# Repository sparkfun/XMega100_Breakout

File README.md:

SparkFun XMega100 Breakout
========================================

[*SparkFun XMega100 Breakout (BOB-09546)*](https://www.sparkfun.com/products/9546)

This is a breakout board for the 100-pin TQFP package of Atmel’s ATxmega128A1. 
The ATxmega128A1 is a low power, high performance and peripheral rich CMOS 8/16-bit microcontroller based on the AVR enhanced RISC architecture.

Repository Contents
-------------------

* **/Firmware** - Example code 
* **/Hardware** - Eagle design files (.brd, .sch)
* **/Production** - Production panel files (.brd)

Documentation
--------------
* **[SparkFun Fritzing repo](https://github.com/sparkfun/Fritzing_Parts)** - Fritzing diagrams for SparkFun products.
* **[SparkFun 3D Model repo](https://github.com/sparkfun/3D_Models)** - 3D models of SparkFun products. 

License Information
-------------------
This product is _**open source**_! 

The **hardware** is released under [Creative Commons ShareAlike 4.0 International](https://creativecommons.org/licenses/by-sa/4.0/).

The **code** is beerware; if you see me (or any other SparkFun employee) at the local, and you've found our code helpful, please buy us a round!

Please use, reuse, and modify these files as you see fit. Please maintain attribution to SparkFun Electronics and release anything derivative under the same license.

Distributed as-is; no warranty is given.

- Your friends at SparkFun.

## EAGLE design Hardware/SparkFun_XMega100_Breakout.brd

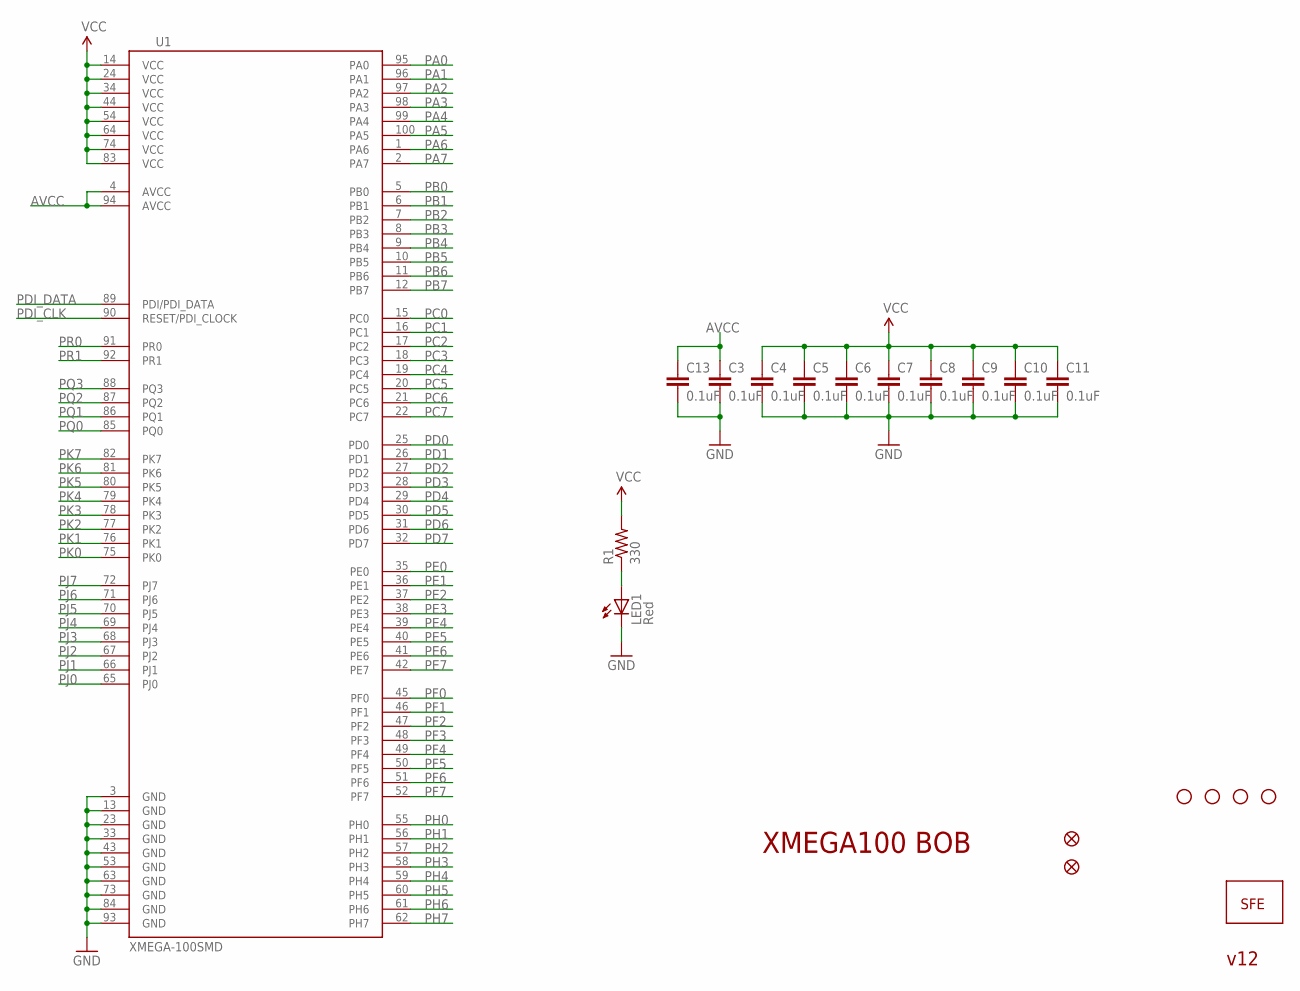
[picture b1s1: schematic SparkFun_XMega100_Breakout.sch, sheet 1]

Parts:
C3, C4, C5, C6, C7, C8, C9, C10, C11, C13: 0.1uF; 0402-CAP
JP1: LOGO-SFENEW; SFE-NEW-WEBLOGO
JP2, JP3, JP4, JP5: STAND-OFF
JP12, JP13: FIDUCIAL1X2; FIDUCIAL-1X2
LED1: Red; LED-0603
R1: 330; 0402-RES
U1: XMEGA-100SMD; TQFP-100-14X14MM

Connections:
AVCC: C3.1, C13.1, U1.4 (AVCC), U1.94 (AVCC); also elsewhere on the board
GND: C3.2, C4.2, C5.2, C6.2, C7.2, C8.2, C9.2, C10.2, C11.2, C13.2, LED1.C, U1.3 (GND), U1.13 (GND), U1.23 (GND), U1.33 (GND), U1.43 (GND), U1.53 (GND), U1.63 (GND), U1.73 (GND), U1.84 (GND), U1.93 (GND); also elsewhere on the board
unnamed: LED1.A, R1.1
PA0: U1.95 (PA0); also elsewhere on the board
PA1: U1.96 (PA1); also elsewhere on the board
PA2: U1.97 (PA2); also elsewhere on the board
PA3: U1.98 (PA3); also elsewhere on the board
PA4: U1.99 (PA4); also elsewhere on the board
PA5: U1.100 (PA5); also elsewhere on the board
PA6: U1.1 (PA6); also elsewhere on the board
PA7: U1.2 (PA7); also elsewhere on the board
PB0: U1.5 (PB0); also elsewhere on the board
PB1: U1.6 (PB1); also elsewhere on the board
PB2: U1.7 (PB2); also elsewhere on the board
PB3: U1.8 (PB3); also elsewhere on the board
PB4: U1.9 (PB4); also elsewhere on the board
PB5: U1.10 (PB5); also elsewhere on the board
PB6: U1.11 (PB6); also elsewhere on the board
PB7: U1.12 (PB7); also elsewhere on the board
PC0: U1.15 (PC0); also elsewhere on the board
PC1: U1.16 (PC1); also elsewhere on the board
PC2: U1.17 (PC2); also elsewhere on the board
PC3: U1.18 (PC3); also elsewhere on the board
PC4: U1.19 (PC4); also elsewhere on the board
PC5: U1.20 (PC5); also elsewhere on the board
PC6: U1.21 (PC6); also elsewhere on the board
PC7: U1.22 (PC7); also elsewhere on the board
PD0: U1.25 (PD0); also elsewhere on the board
PD1: U1.26 (PD1); also elsewhere on the board
PD2: U1.27 (PD2); also elsewhere on the board
PD3: U1.28 (PD3); also elsewhere on the board
PD4: U1.29 (PD4); also elsewhere on the board
PD5: U1.30 (PD5); also elsewhere on the board
PD6: U1.31 (PD6); also elsewhere on the board
PD7: U1.32 (PD7); also elsewhere on the board
PDI_CLK: U1.90 (RESET/PDI_CLOCK); also elsewhere on the board
PDI_DATA: U1.89 (PDI/PDI_DATA); also elsewhere on the board
PE0: U1.35 (PE0); also elsewhere on the board
PE1: U1.36 (PE1); also elsewhere on the board
PE2: U1.37 (PE2); also elsewhere on the board
PE3: U1.38 (PE3); also elsewhere on the board
PE4: U1.39 (PE4); also elsewhere on the board
PE5: U1.40 (PE5); also elsewhere on the board
PE6: U1.41 (PE6); also elsewhere on the board
PE7: U1.42 (PE7); also elsewhere on the board
PF0: U1.45 (PF0); also elsewhere on the board
PF1: U1.46 (PF1); also elsewhere on the board
PF2: U1.47 (PF2); also elsewhere on the board
PF3: U1.48 (PF3); also elsewhere on the board
PF4: U1.49 (PF4); also elsewhere on the board
PF5: U1.50 (PF5); also elsewhere on the board
PF6: U1.51 (PF6); also elsewhere on the board
PF7: U1.52 (PF7); also elsewhere on the board
PH0: U1.55 (PH0); also elsewhere on the board
PH1: U1.56 (PH1); also elsewhere on the board
PH2: U1.57 (PH2); also elsewhere on the board
PH3: U1.58 (PH3); also elsewhere on the board
PH4: U1.59 (PH4); also elsewhere on the board
PH5: U1.60 (PH5); also elsewhere on the board
PH6: U1.61 (PH6); also elsewhere on the board
PH7: U1.62 (PH7); also elsewhere on the board
PJ0: U1.65 (PJ0); also elsewhere on the board
PJ1: U1.66 (PJ1); also elsewhere on the board
PJ2: U1.67 (PJ2); also elsewhere on the board
PJ3: U1.68 (PJ3); also elsewhere on the board
PJ4: U1.69 (PJ4); also elsewhere on the board
PJ5: U1.70 (PJ5); also elsewhere on the board
PJ6: U1.71 (PJ6); also elsewhere on the board
PJ7: U1.72 (PJ7); also elsewhere on the board
PK0: U1.75 (PK0); also elsewhere on the board
PK1: U1.76 (PK1); also elsewhere on the board
PK2: U1.77 (PK2); also elsewhere on the board
PK3: U1.78 (PK3); also elsewhere on the board
PK4: U1.79 (PK4); also elsewhere on the board
PK5: U1.80 (PK5); also elsewhere on the board
PK6: U1.81 (PK6); also elsewhere on the board
PK7: U1.82 (PK7); also elsewhere on the board
PQ0: U1.85 (PQ0); also elsewhere on the board
PQ1: U1.86 (PQ1); also elsewhere on the board
PQ2: U1.87 (PQ2); also elsewhere on the board
PQ3: U1.88 (PQ3); also elsewhere on the board
PR0: U1.91 (PR0); also elsewhere on the board
PR1: U1.92 (PR1); also elsewhere on the board
VCC: C4.1, C5.1, C6.1, C7.1, C8.1, C9.1, C10.1, C11.1, R1.2, U1.14 (VCC), U1.24 (VCC), U1.34 (VCC), U1.44 (VCC), U1.54 (VCC), U1.64 (VCC), U1.74 (VCC), U1.83 (VCC); also elsewhere on the board

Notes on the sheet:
XMEGA100 BOB
v12

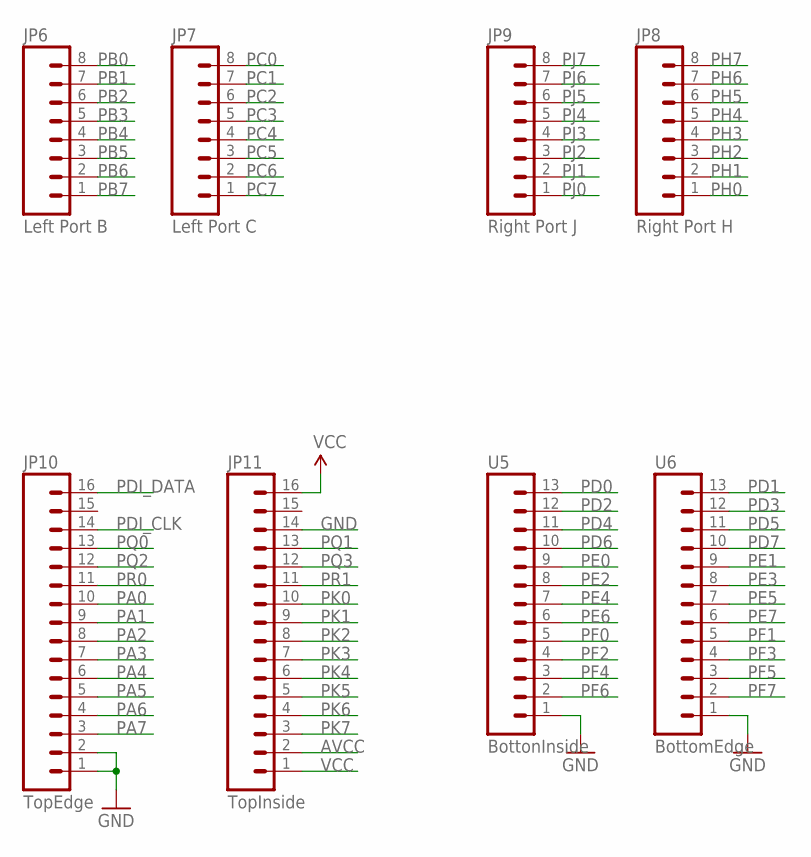
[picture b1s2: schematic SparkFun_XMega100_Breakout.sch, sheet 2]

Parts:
JP6: Left Port B; 1X08
JP7: Left Port C; 1X08
JP8: Right Port H; 1X08
JP9: Right Port J; 1X08
JP10: TopEdge; 1X16
JP11: TopInside; 1X16
U5: BottonInside; 1X13
U6: BottomEdge; 1X13

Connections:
AVCC: JP11.2; also elsewhere on the board
GND: JP10.1, JP10.2, JP11.14, U5.1, U6.1; also elsewhere on the board
PA0: JP10.10; also elsewhere on the board
PA1: JP10.9; also elsewhere on the board
PA2: JP10.8; also elsewhere on the board
PA3: JP10.7; also elsewhere on the board
PA4: JP10.6; also elsewhere on the board
PA5: JP10.5; also elsewhere on the board
PA6: JP10.4; also elsewhere on the board
PA7: JP10.3; also elsewhere on the board
PB0: JP6.8; also elsewhere on the board
PB1: JP6.7; also elsewhere on the board
PB2: JP6.6; also elsewhere on the board
PB3: JP6.5; also elsewhere on the board
PB4: JP6.4; also elsewhere on the board
PB5: JP6.3; also elsewhere on the board
PB6: JP6.2; also elsewhere on the board
PB7: JP6.1; also elsewhere on the board
PC0: JP7.8; also elsewhere on the board
PC1: JP7.7; also elsewhere on the board
PC2: JP7.6; also elsewhere on the board
PC3: JP7.5; also elsewhere on the board
PC4: JP7.4; also elsewhere on the board
PC5: JP7.3; also elsewhere on the board
PC6: JP7.2; also elsewhere on the board
PC7: JP7.1; also elsewhere on the board
PD0: U5.13; also elsewhere on the board
PD1: U6.13; also elsewhere on the board
PD2: U5.12; also elsewhere on the board
PD3: U6.12; also elsewhere on the board
PD4: U5.11; also elsewhere on the board
PD5: U6.11; also elsewhere on the board
PD6: U5.10; also elsewhere on the board
PD7: U6.10; also elsewhere on the board
PDI_CLK: JP10.14; also elsewhere on the board
PDI_DATA: JP10.16; also elsewhere on the board
PE0: U5.9; also elsewhere on the board
PE1: U6.9; also elsewhere on the board
PE2: U5.8; also elsewhere on the board
PE3: U6.8; also elsewhere on the board
PE4: U5.7; also elsewhere on the board
PE5: U6.7; also elsewhere on the board
PE6: U5.6; also elsewhere on the board
PE7: U6.6; also elsewhere on the board
PF0: U5.5; also elsewhere on the board
PF1: U6.5; also elsewhere on the board
PF2: U5.4; also elsewhere on the board
PF3: U6.4; also elsewhere on the board
PF4: U5.3; also elsewhere on the board
PF5: U6.3; also elsewhere on the board
PF6: U5.2; also elsewhere on the board
PF7: U6.2; also elsewhere on the board
PH0: JP8.1; also elsewhere on the board
PH1: JP8.2; also elsewhere on the board
PH2: JP8.3; also elsewhere on the board
PH3: JP8.4; also elsewhere on the board
PH4: JP8.5; also elsewhere on the board
PH5: JP8.6; also elsewhere on the board
PH6: JP8.7; also elsewhere on the board
PH7: JP8.8; also elsewhere on the board
PJ0: JP9.1; also elsewhere on the board
PJ1: JP9.2; also elsewhere on the board
PJ2: JP9.3; also elsewhere on the board
PJ3: JP9.4; also elsewhere on the board
PJ4: JP9.5; also elsewhere on the board
PJ5: JP9.6; also elsewhere on the board
PJ6: JP9.7; also elsewhere on the board
PJ7: JP9.8; also elsewhere on the board
PK0: JP11.10; also elsewhere on the board
PK1: JP11.9; also elsewhere on the board
PK2: JP11.8; also elsewhere on the board
PK3: JP11.7; also elsewhere on the board
PK4: JP11.6; also elsewhere on the board
PK5: JP11.5; also elsewhere on the board
PK6: JP11.4; also elsewhere on the board
PK7: JP11.3; also elsewhere on the board
PQ0: JP10.13; also elsewhere on the board
PQ1: JP11.13; also elsewhere on the board
PQ2: JP10.12; also elsewhere on the board
PQ3: JP11.12; also elsewhere on the board
PR0: JP10.11; also elsewhere on the board
PR1: JP11.11; also elsewhere on the board
VCC: JP11.1, JP11.16; also elsewhere on the board

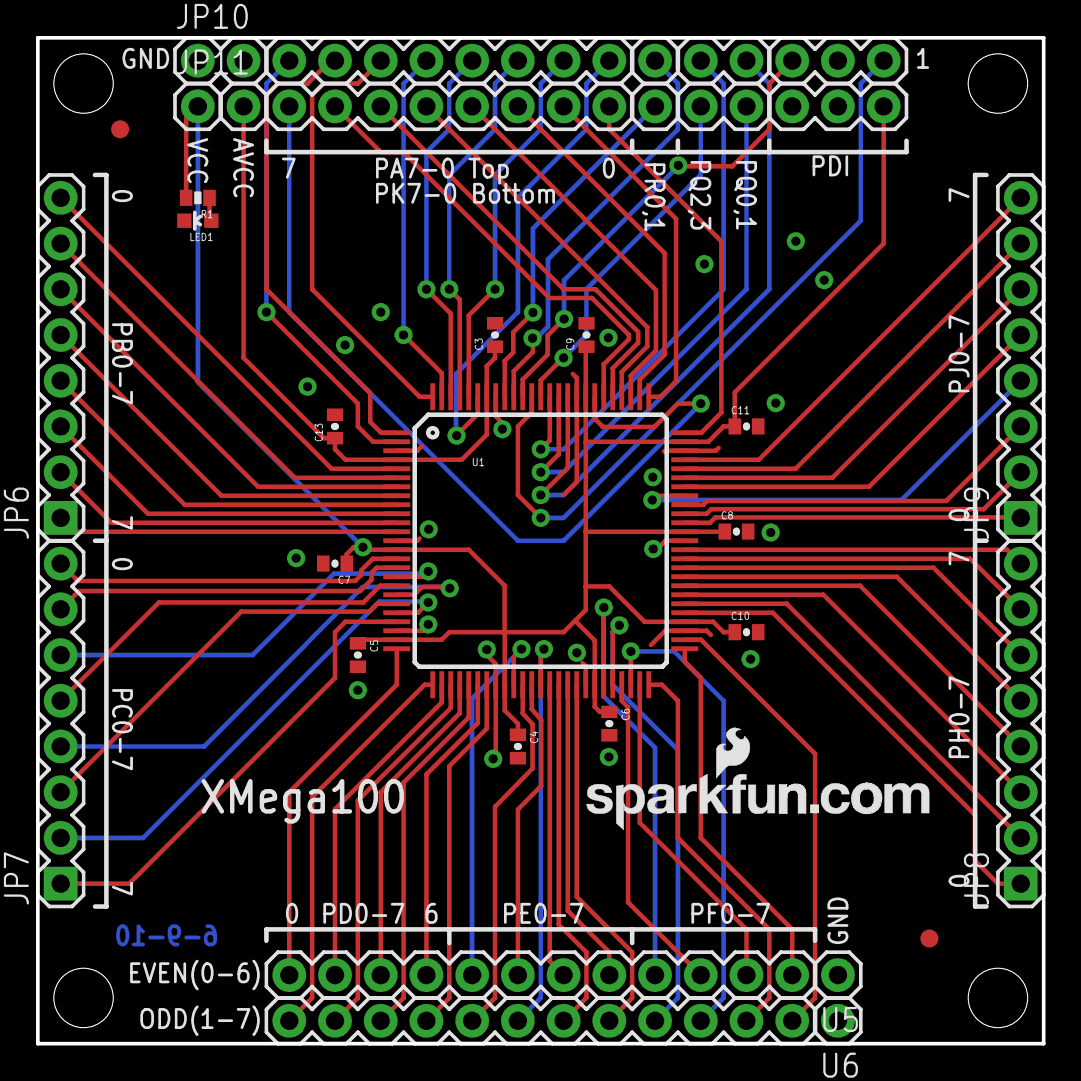
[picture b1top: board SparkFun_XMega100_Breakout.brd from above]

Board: 2 copper layers, 55.9 x 55.9 mm, 28 parts (0 on the bottom side), 84 nets.

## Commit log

2015-05-12 Adding hardware files, example C
